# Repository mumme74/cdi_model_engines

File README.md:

# CDI for model engines
A CDI driven by 12v to be used by model engines

# Warning this project isnt tested nor testbuilt yet

Its for my brother next model engine that he's building, a Hoglet.

Features:
 * Should (in theory) support a 12Cyl up to 6000 rpm
 * 2 wire hallsensor solution (like a GME)
 * Hallsensor trigger output to optional other board (like a arduino)
 * Optionally trigger from a input instead of hallsensor (remove a solder bridge)

Should be able to run his challenger V8
https://www.youtube.com/watch?v=TyKyQjUpV_E

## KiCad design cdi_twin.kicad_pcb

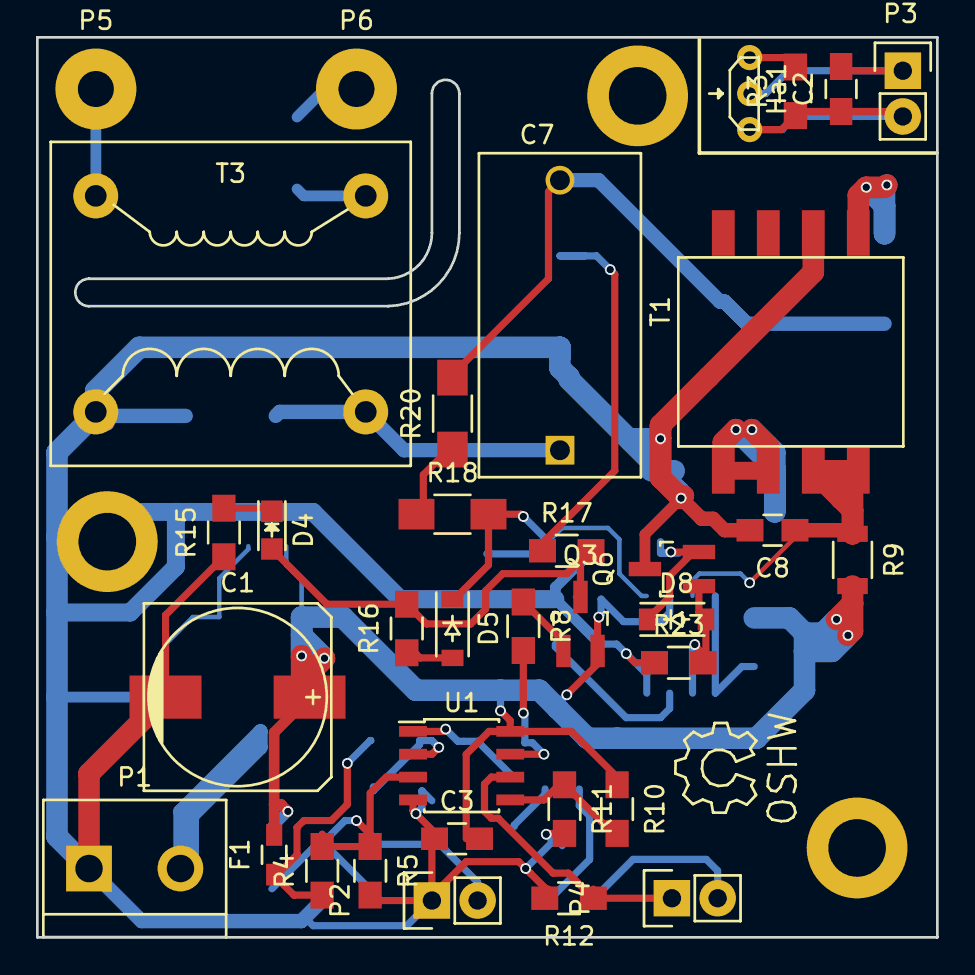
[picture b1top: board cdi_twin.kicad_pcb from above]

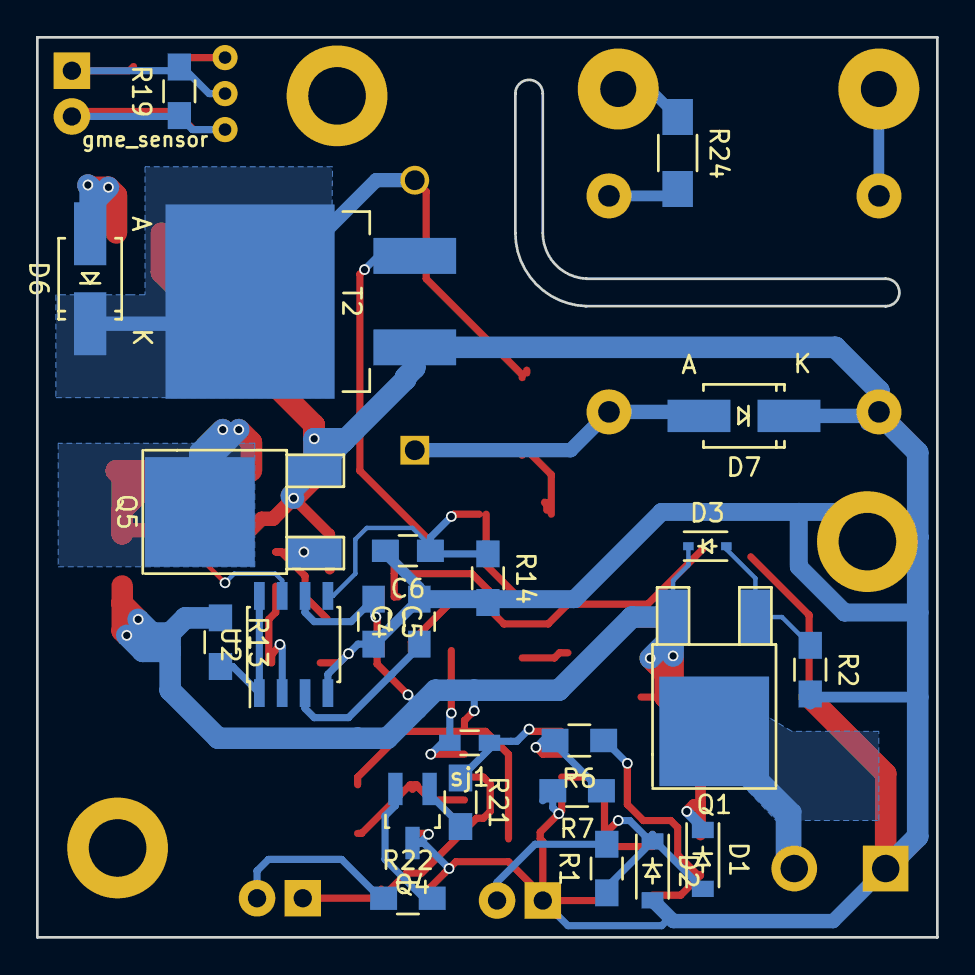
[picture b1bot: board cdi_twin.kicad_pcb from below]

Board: 2 copper layers, 50.0 x 50.0 mm, 59 parts (24 on the bottom side), 35 nets.

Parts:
C1: 470u; c_elec_10x10
C2, C4: 1n; C_0805_HandSoldering
C3, C5, C6: 100n; C_0805_HandSoldering
C7: 1.5u 400v; C_Rect_L18_W9_H15_P15
C8: C; C_0805_HandSoldering
D1, D2, D8: 1n4148w; SOD-123
D3: 10v; SOD-323
D4: LED; LED_0805
D5: 1n4148; SOD-123
D6: RFN2L4STE25; SMA_Handsoldering
D7: S1M-13-F; SMA_Handsoldering
F1: PTC_33ohm; R_0603_HandSoldering
Ha1: DRV5023; hall_to92
P1: power_intake; bornier2
P2, P3: gme_sensor; Pin_Header_Straight_1x02
P4: digital_in; Pin_Header_Straight_1x02
P5, P6: CONN_01X01; SolderWirePad_single_2mmDrill
Q1: Q_PMOS_GDS; TO-252-2Lead
Q3, Q4, Q6: BC857; SOT-23_Handsoldering
Q5: IRFR7546PBF; TO-252-2Lead
R1, R13, R16: 10; R_0805_HandSoldering
R2, R7, R10, R12, R19, R21: 10k; R_0805_HandSoldering
R3, R5, R14: 1.2k; R_0805_HandSoldering
R4: 100; R_0805_HandSoldering
R6: 1.8k; R_0805_HandSoldering
R8, R11, R15, R17, R23: 1k; R_0805_HandSoldering
R9: 0.033; R_1206
R18, R20: 150k; R_1206_HandSoldering
R22: 150; R_0805_HandSoldering
R24: 4.7k; R_1206_HandSoldering
T1: transformer_PA1134NLT; EP10_transformer
T2: BT152B-600R; TO-263-2Lead
T3: ign_coil HY-CD6; HY-CD6_trafo
U1: LM2903; SOIC-8_3.9x4.9mm_Pitch1.27mm
U2: MC34063; SOIC-8_3.9x4.9mm_Pitch1.27mm
sj1: ext_trigg; R_0603_HandSoldering

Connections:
/+12v: C1.1, C3.2, C5.1, D1.1, D3.1, F1.2, Q1.3, Q3.2, R9.2, R10.1, R13.1, U1.8, U2.6
/gme+: C2.1, Ha1.1, P2.2, P3.2, R1.2, R3.1, R19.1
/trigger_in: P4.1, R12.1, U1.6
/trigger_out_inv: P4.2, R22.1
GND: C1.2, C2.2, C3.1, C4.2, C5.2, C6.2, C8.2, D2.2, D7.1, Ha1.2, P1.1, P2.1, P3.1, Q4.3, Q5.3, Q6.3, R2.2, R5.2, R7.2, R11.2, R12.2, R14.2, R15.1, R19.2, R23.1, T1.3, T2.1, T3.2, U1.4, U2.4
unnamed: C4.1, U2.3
unnamed: C6.1, D5.1, R14.1, R18.2, U2.5
unnamed: C7.1, D7.2, T3.1
unnamed: C7.2, D6.1, R20.2, T2.2
unnamed: C8.1, R9.1, T1.5, T1.6, U2.7
unnamed: D1.2, D2.1, R1.1, R4.2, R5.1, U1.3
unnamed: D3.2, Q1.1, R2.1
unnamed: D4.1, R15.2
unnamed: D4.2, Q3.3, R16.2, R17.2
unnamed: D5.2, R16.1
unnamed: D6.2, T1.4
unnamed: D8.1, Q5.1, Q6.2
unnamed: D8.2, Q6.1, R23.2, U2.2
unnamed: F1.1, R4.1, R6.1
unnamed: Ha1.3, R3.2
unnamed: P1.2, Q1.2
unnamed: P5.1, T3.3
unnamed: P6.1, R24.1
unnamed: Q3.1, R8.1
unnamed: Q4.1, R21.2
unnamed: Q4.2, R22.2
unnamed: Q5.2, T1.7, T1.8
unnamed: R6.2, R7.1, U1.2
unnamed: R8.2, U1.7, sj1.2
unnamed: R10.2, R11.1, U1.5
unnamed: R13.2, U2.1, U2.8
unnamed: R17.1, T2.3
unnamed: R18.1, R20.1
unnamed: R21.1, U1.1, sj1.1
unnamed: R24.2, T3.4
